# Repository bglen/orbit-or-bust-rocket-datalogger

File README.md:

# Rocket Datalogger

This is an STM32-based model rocket datalogger. It logs from the following sensors:

- DAN-F10-00B ublox dual band GNSS module
- ADXL375 high G accelerometer
- BNO055 9-DOF inertial measurement unit
- MS5607-02BA high resolution altimeter sensor
- BME280 humidity, pressure and temperature sensor

The board is powered from a single 1S LiPo battery with a standard JST-PH connector. A USB-C connector is provided for downloading the flight data. a 6-pin JST-PH connector is provided to extend the device's functionality with 6 3.3V-level GPIO pins.

The GNSS module is on a seperate PCB connected with a JST-PH connector, to give the integrated antenna the appropriate orientation (facing the sky).

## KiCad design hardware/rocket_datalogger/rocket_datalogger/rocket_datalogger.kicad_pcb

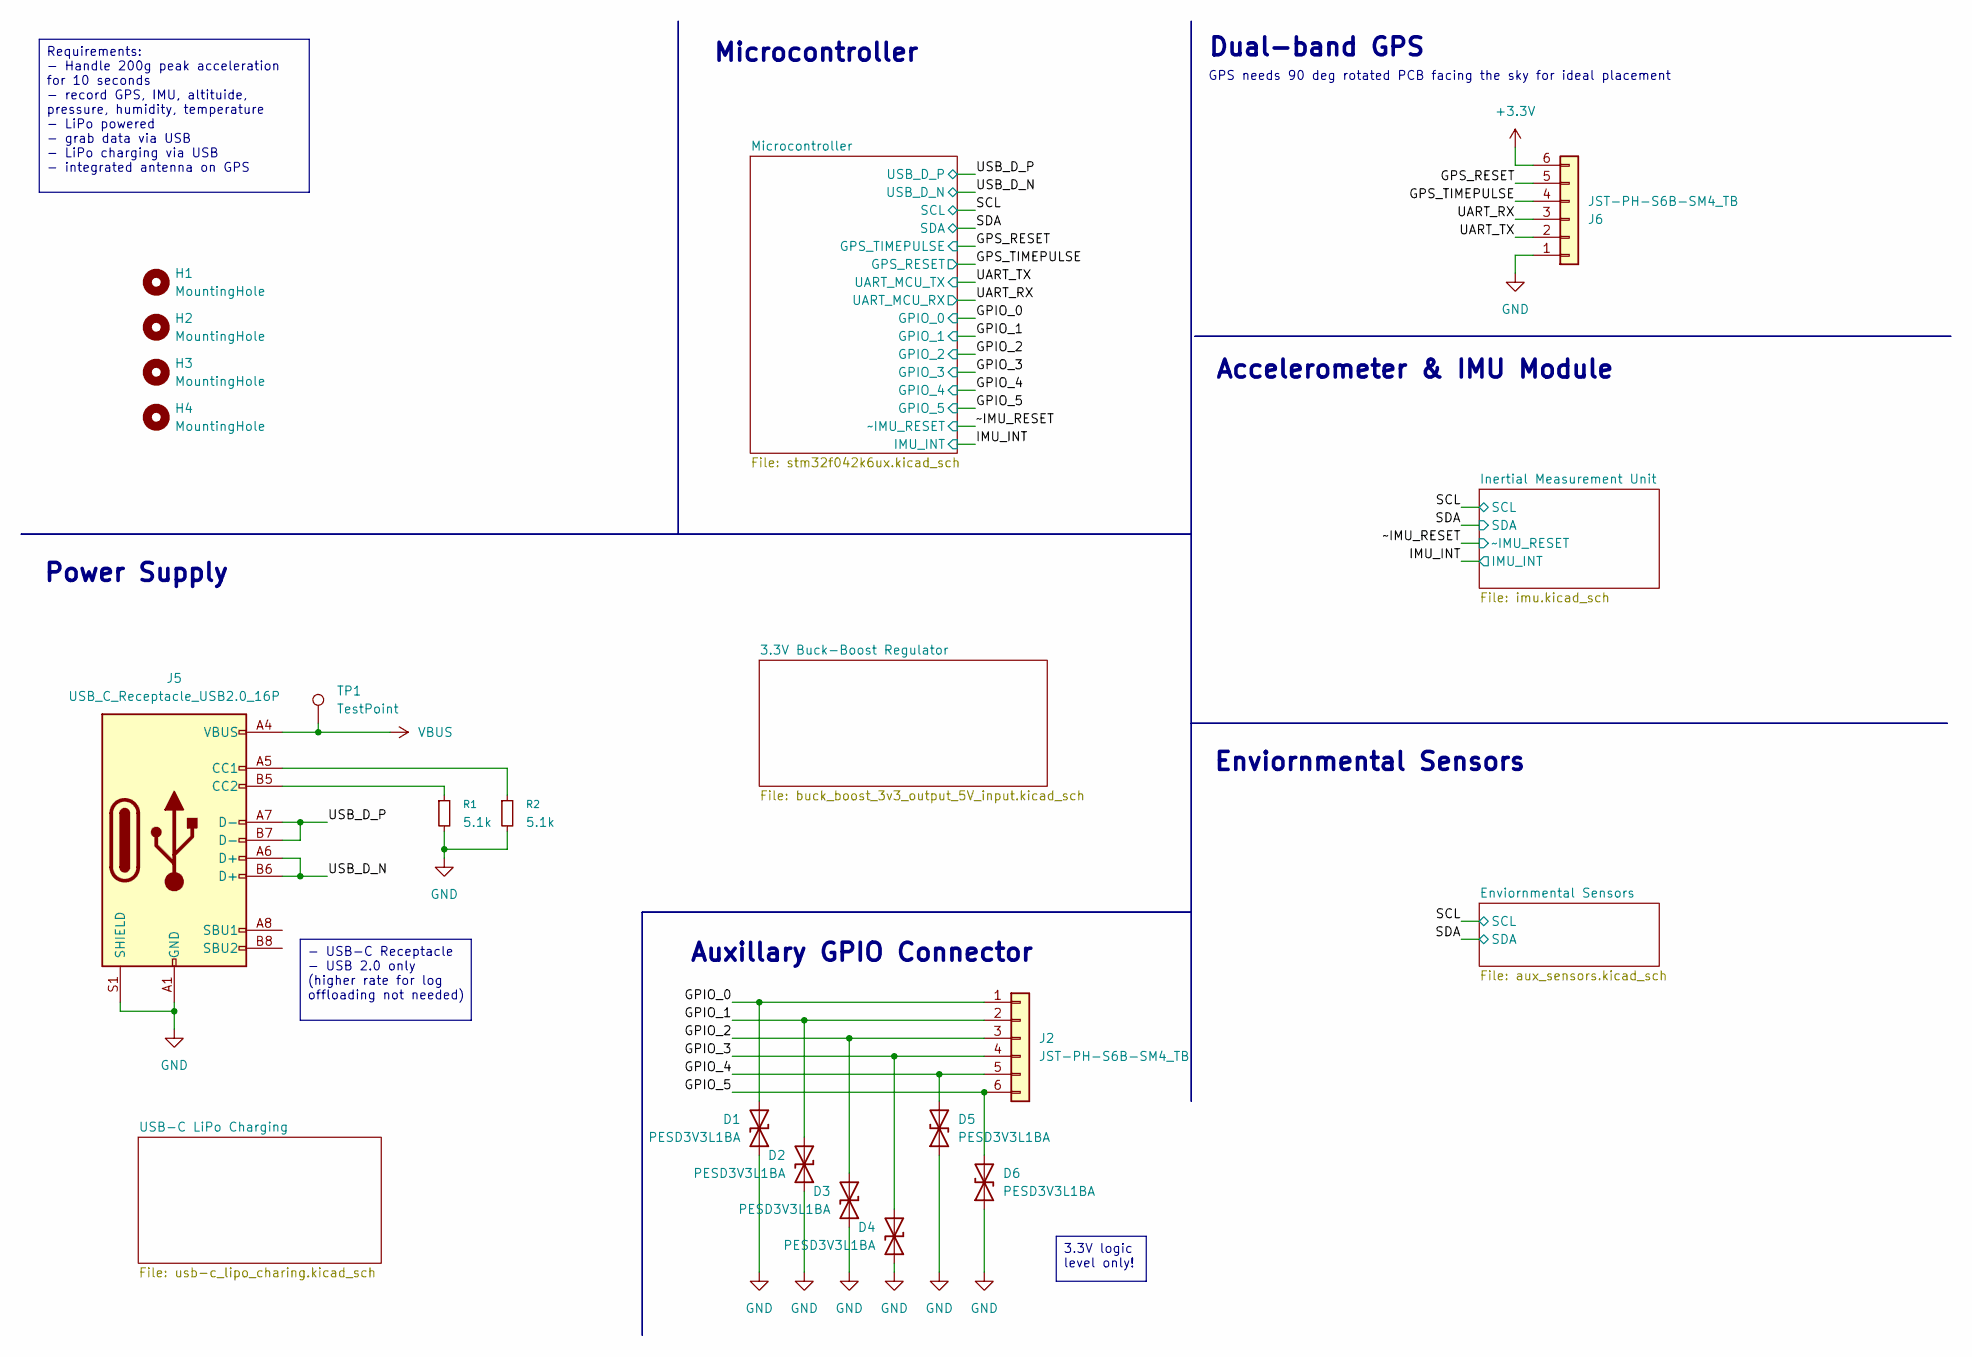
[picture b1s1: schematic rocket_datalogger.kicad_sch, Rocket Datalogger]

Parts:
D1, D2, D3, D4, D5, D6: PESD3V3L1BA; D_SOD-323
H1, H2, H3, H4: MountingHole; MountingHole_3.2mm_M3
J2, J6: JST-PH-S6B-SM4_TB; JST_PH_S6B-PH-SM4-TB_1x06-1MP_P2.00mm_Horizontal
J5: USB_C_Receptacle_USB2.0_16P; USB_C_Receptacle_GCT_USB4105-xx-A_16P_TopMnt_Horizontal
R1, R2: 5.1k; R_0603_1608Metric
TP1: TestPoint; TestPoint_Pad_D2.0mm

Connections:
+3.3V: J6.6; also elsewhere on the board
/GPIO_0: D1.2 (A2), J2.1; also elsewhere on the board
/GPIO_1: D2.2 (A2), J2.2; also elsewhere on the board
/GPIO_2: D3.2 (A2), J2.3; also elsewhere on the board
/GPIO_3: D4.2 (A2), J2.4; also elsewhere on the board
/GPIO_4: D5.2 (A2), J2.5; also elsewhere on the board
/GPIO_5: D6.2 (A2), J2.6; also elsewhere on the board
/GPS_RESET: J6.5; also elsewhere on the board
/GPS_TIMEPULSE: J6.4; also elsewhere on the board
/UART_RX: J6.3; also elsewhere on the board
/UART_TX: J6.2; also elsewhere on the board
/USB_D_N: J5.A6 (D+), J5.B6 (D+); also elsewhere on the board
/USB_D_P: J5.A7 (D-), J5.B7 (D-); also elsewhere on the board
GND: D1.1 (A1), D2.1 (A1), D3.1 (A1), D4.1 (A1), D5.1 (A1), D6.1 (A1), J5.A1 (GND), J5.A12 (GND), J5.B1 (GND), J5.B12 (GND), J5.S1 (SHIELD), J6.1, R1.2, R2.2; also elsewhere on the board
unnamed: J5.A5 (CC1), R2.1
unnamed: J5.B5 (CC2), R1.1
VBUS: J5.A4 (VBUS), J5.A9 (VBUS), J5.B4 (VBUS), J5.B9 (VBUS), TP1.1; also elsewhere on the board

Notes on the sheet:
Auxillary GPIO Connector
Dual-band GPS
Power Supply
GPS needs 90 deg rotated PCB facing the sky for ideal placement
Enviornmental Sensors
Microcontroller
Accelerometer & IMU Module
- USB-C Receptacle - USB 2.0 only (higher rate for log offloading not needed)
Requirements: - Handle 200g peak acceleration for 10 seconds - record GPS, IMU, altituide, pressure, humidity, temperature - LiPo powered - grab data via USB - LiPo charging via USB - integrated antenna on GPS
3.3V logic level only!

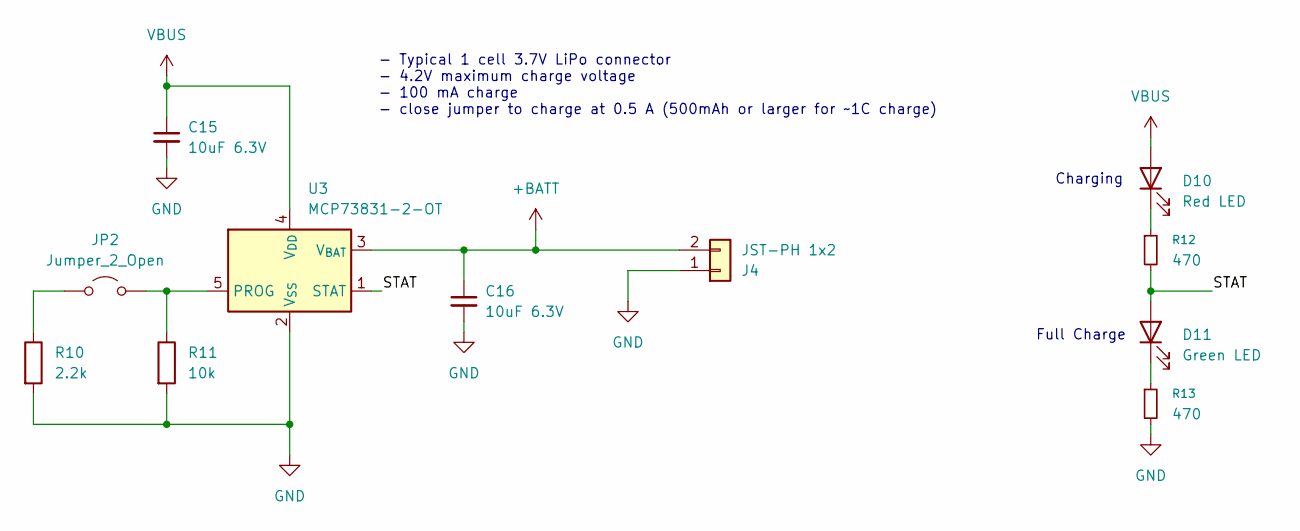
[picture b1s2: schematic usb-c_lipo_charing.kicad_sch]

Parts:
C15, C16: 10uF 6.3V; C_0603_1608Metric
D10: Red LED; LED_0603_1608Metric
D11: Green LED; LED_0603_1608Metric
J4: JST-PH 1x2; JST_PH_S2B-PH-K_1x02_P2.00mm_Horizontal
JP2: Jumper_2_Open; SolderJumper-2_P1.3mm_Open_RoundedPad1.0x1.5mm
R10: 2.2k; R_0603_1608Metric
R11: 10k; R_0603_1608Metric
R12, R13: 470; R_0603_1608Metric
U3: MCP73831-2-OT; SOT-23-5

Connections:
+BATT: C16.1, J4.2, U3.3 (V_{BAT}); also elsewhere on the board
/USB-C LiPo Charging/STAT: D11.2 (A), R12.2, U3.1 (STAT)
GND: C15.2, C16.2, J4.1, R10.2, R11.2, R13.2, U3.2 (V_{SS}); also elsewhere on the board
unnamed: D10.1 (K), R12.1
unnamed: D11.1 (K), R13.1
unnamed: JP2.1 (A), R10.1
unnamed: JP2.2 (B), R11.1, U3.5 (PROG)
VBUS: C15.1, D10.2 (A), U3.4 (V_{DD}); also elsewhere on the board

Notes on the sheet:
- Typical 1 cell 3.7V LiPo connector - 4.2V maximum charge voltage - 100 mA charge - close jumper to charge at 0.5 A (500mAh or larger for ~1C charge)
Charging
Full Charge

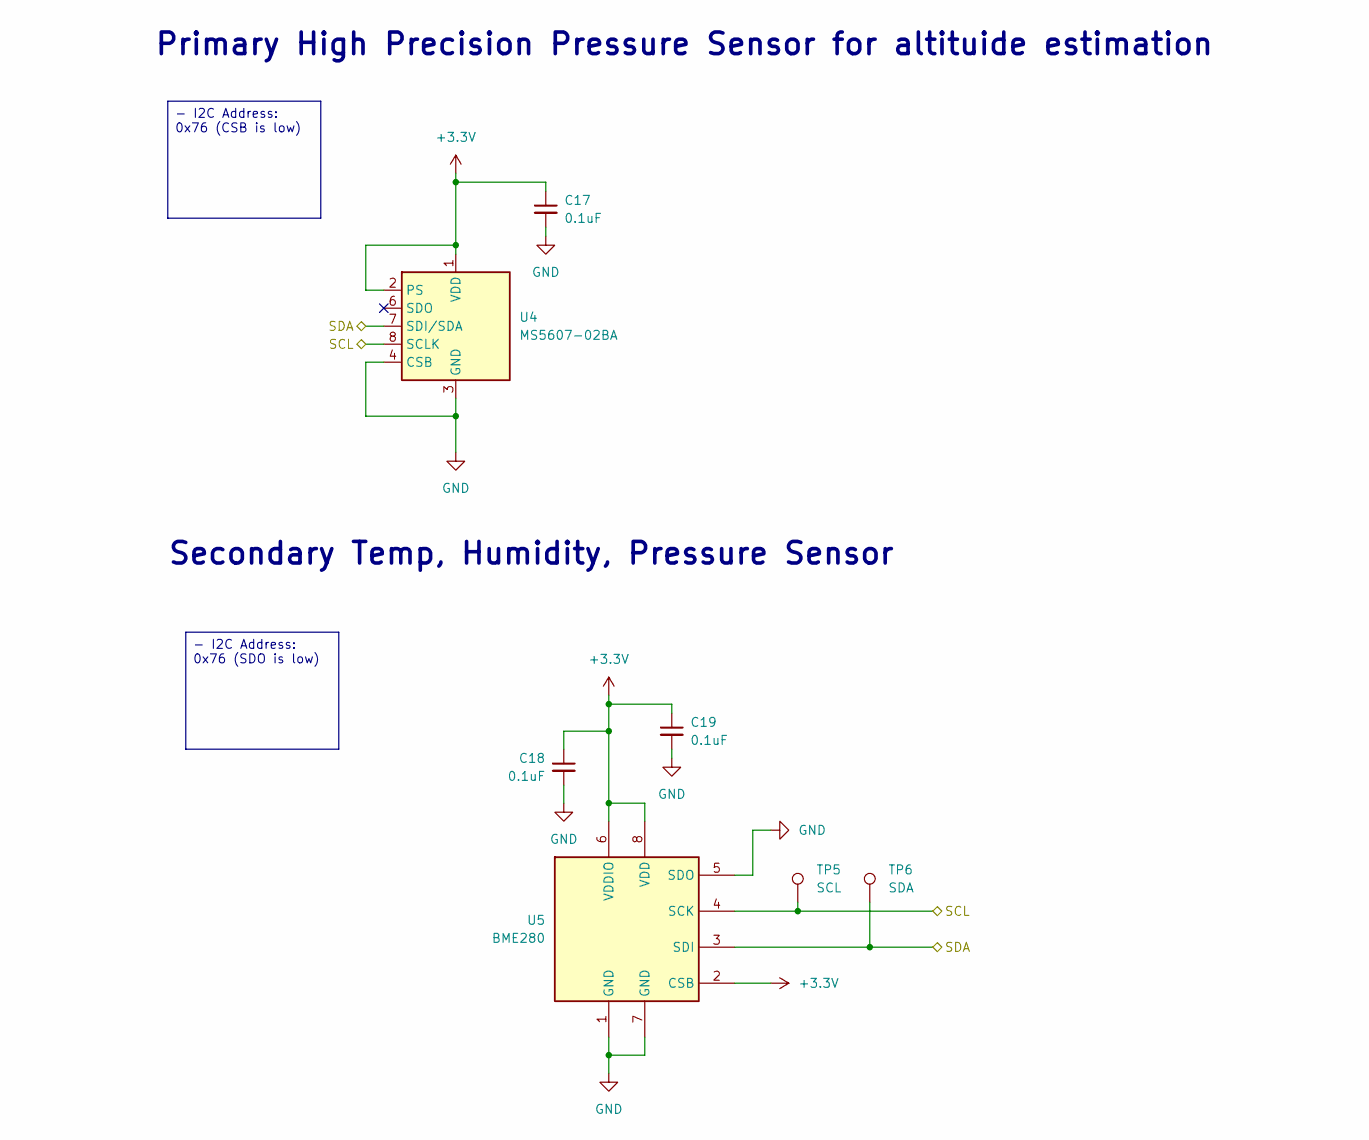
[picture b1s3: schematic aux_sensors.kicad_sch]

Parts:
C17, C18, C19: 0.1uF; C_0603_1608Metric
TP5: SCL; TestPoint_Pad_D2.0mm
TP6: SDA; TestPoint_Pad_D2.0mm
U4: MS5607-02BA; LGA-8_3x5mm_P1.25mm
U5: BME280; Bosch_LGA-8_2.5x2.5mm_P0.65mm_ClockwisePinNumbering

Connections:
+3.3V: C17.1, C18.1, C19.1, U4.1 (VDD), U4.2 (PS), U5.2 (CSB), U5.6 (VDDIO), U5.8 (VDD); also elsewhere on the board
/SCL: TP5.1, U4.8 (SCLK), U5.4 (SCK); also elsewhere on the board
/SDA: TP6.1, U4.7 (SDI/SDA), U5.3 (SDI); also elsewhere on the board
GND: C17.2, C18.2, C19.2, U4.3 (GND), U4.4 (CSB), U4.5 (CSB), U5.1 (GND), U5.5 (SDO), U5.7 (GND); also elsewhere on the board

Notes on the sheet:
Secondary Temp, Humidity, Pressure Sensor
Primary High Precision Pressure Sensor for altituide estimation
- I2C Address: 0x76 (SDO is low)
- I2C Address: 0x76 (CSB is low)

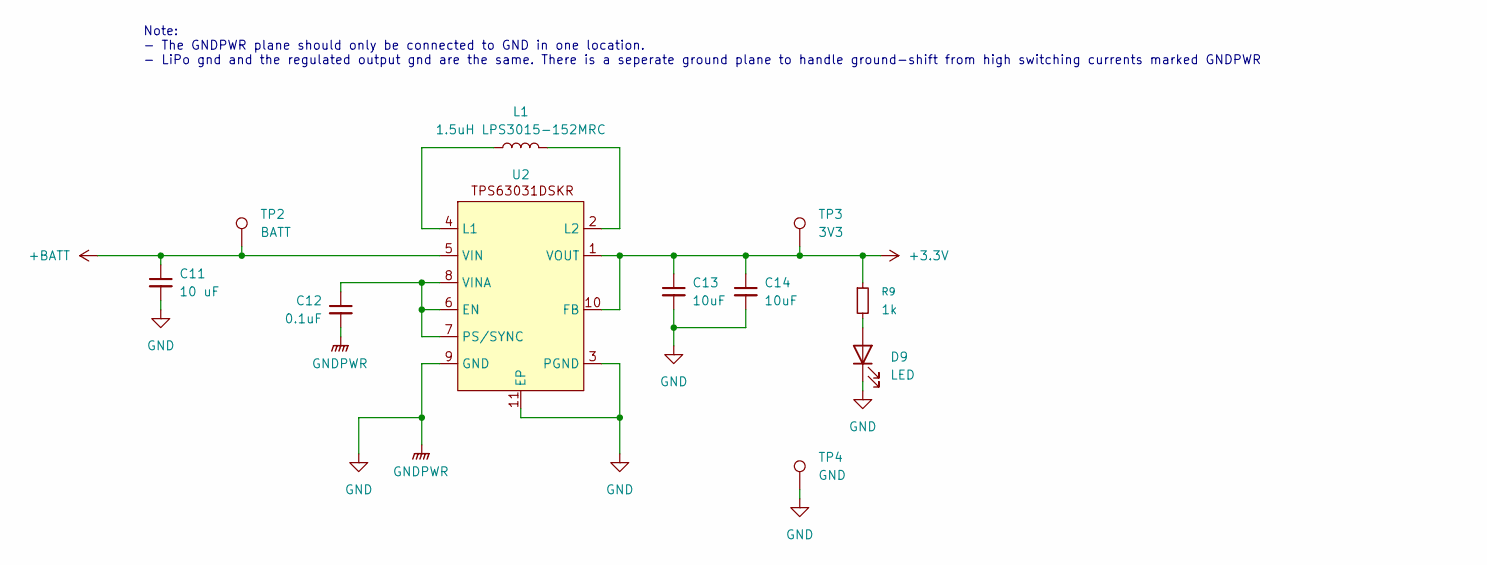
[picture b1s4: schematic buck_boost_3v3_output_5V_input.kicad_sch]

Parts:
C11: 10 uF; C_0603_1608Metric
C12: 0.1uF; C_0603_1608Metric
C13, C14: 10uF; C_0603_1608Metric
D9: LED; LED_0603_1608Metric
L1: 1.5uH LPS3015-152MRC; L_Coilcraft_LPS3010
R9: 1k; R_0603_1608Metric
TP2: BATT; TestPoint_Pad_D2.0mm
TP3: 3V3; TestPoint_Pad_D2.0mm
TP4: GND; TestPoint_Pad_D2.0mm
U2: DSK0010A

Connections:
+3.3V: C13.1, C14.1, R9.1, TP3.1, U2.1 (VOUT), U2.10 (FB); also elsewhere on the board
+BATT: C11.1, TP2.1, U2.5 (VIN); also elsewhere on the board
GND: C11.2, C12.2, C13.2, C14.2, D9.1 (K), TP4.1, U2.3 (PGND), U2.9 (GND), U2.11 (EP); also elsewhere on the board
unnamed: D9.2 (A), R9.2
unnamed: C12.1, U2.6 (EN), U2.7 (PS/SYNC), U2.8 (VINA)
unnamed: L1.1, U2.4 (L1)
unnamed: L1.2, U2.2 (L2)

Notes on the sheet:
Note: - The GNDPWR plane should only be connected to GND in one location. - LiPo gnd and the regulated output gnd are the same. There is a seperate ground plane to handle ground-shift from high switching currents marked GNDPWR

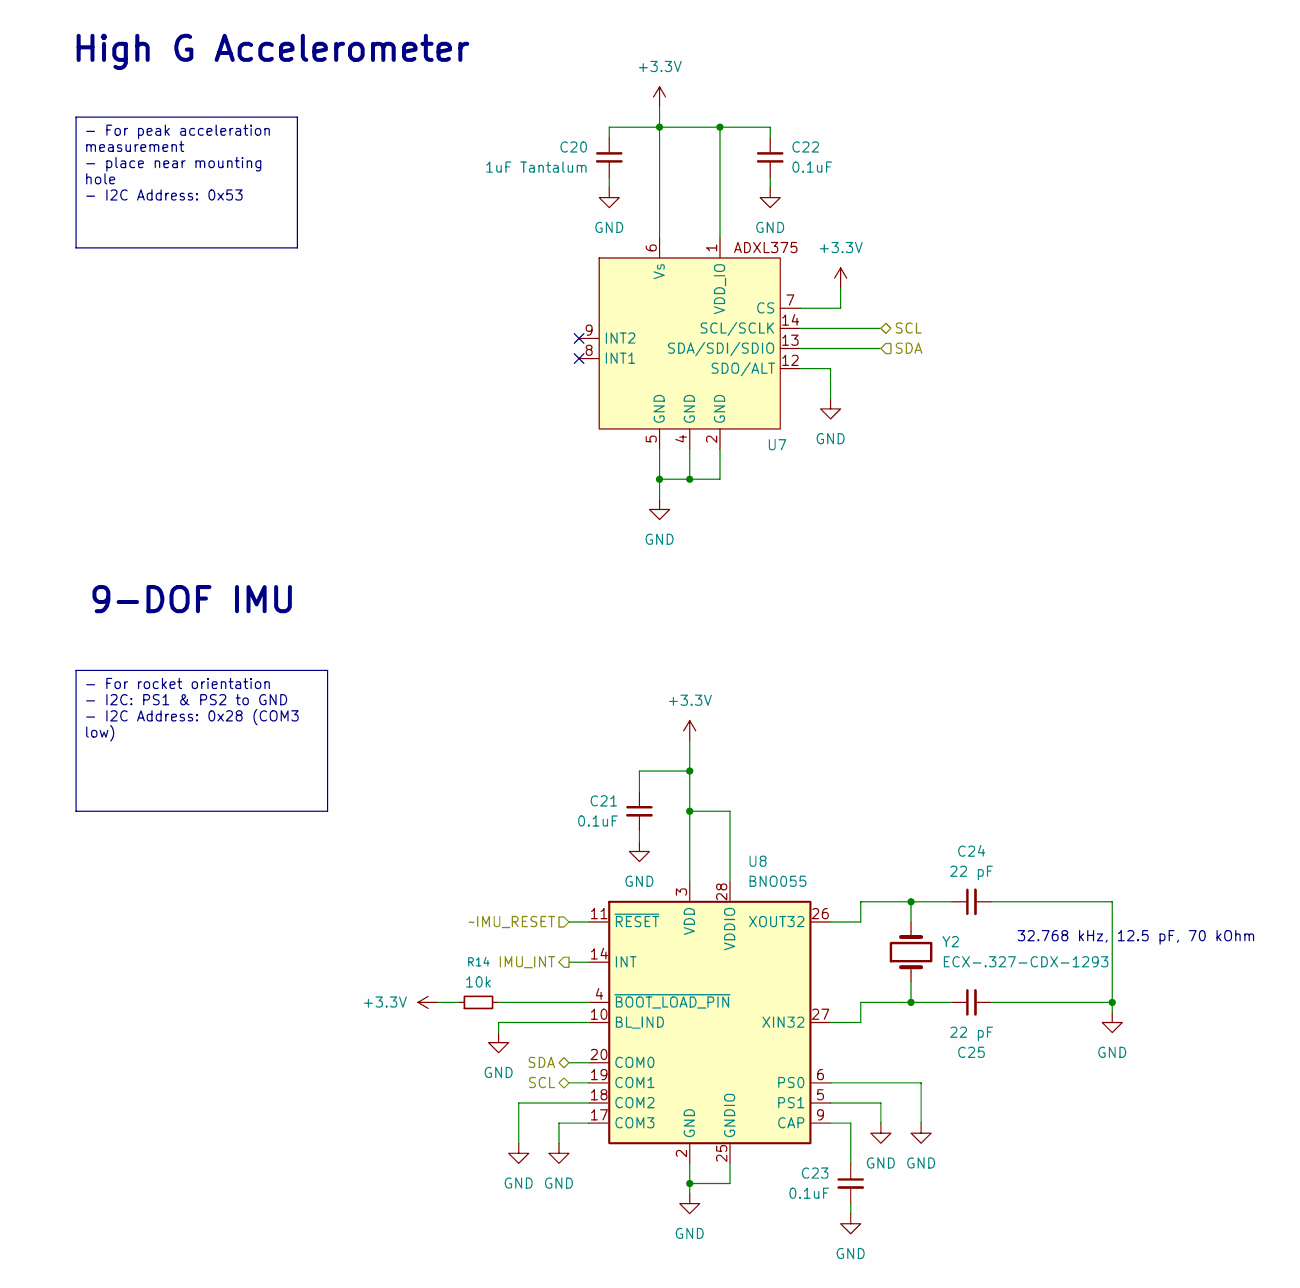
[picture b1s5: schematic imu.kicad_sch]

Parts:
C20: 1uF Tantalum; C_0603_1608Metric
C21, C22, C23: 0.1uF; C_0603_1608Metric
C24, C25: 22 pF; C_0603_1608Metric
R14: 10k; R_0603_1608Metric
U7: LGA-14_3x5mm_P0.8mm_LayoutBorder1x6y
U8: BNO055; LGA-28_5.2x3.8mm_P0.5mm
Y2: ECX-.327-CDX-1293; Crystal_SMD_3215-2Pin_3.2x1.5mm

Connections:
+3.3V: C20.1, C21.1, C22.1, R14.1, U7.1 (VDD_IO), U7.6 (Vs), U7.7 (CS), U8.3 (VDD), U8.28 (VDDIO); also elsewhere on the board
/IMU_INT: U8.14 (INT); also elsewhere on the board
/SCL: U7.14 (SCL/SCLK), U8.19 (COM1); also elsewhere on the board
/SDA: U7.13 (SDA/SDI/SDIO), U8.20 (COM0); also elsewhere on the board
/~IMU_RESET: U8.11 (~RESET); also elsewhere on the board
GND: C20.2, C21.2, C22.2, C23.2, C24.2, C25.2, U7.2 (GND), U7.4 (GND), U7.5 (GND), U7.12 (SDO/ALT), U8.2 (GND), U8.5 (PS1), U8.6 (PS0), U8.10 (BL_IND), U8.17 (COM3), U8.18 (COM2), U8.25 (GNDIO); also elsewhere on the board
unnamed: C23.1, U8.9 (CAP)
unnamed: C25.1, U8.27 (XIN32), Y2.1
unnamed: C24.1, U8.26 (XOUT32), Y2.2
unnamed: R14.2, U8.4 (~BOOT_LOAD_PIN)

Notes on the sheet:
High G Accelerometer
9-DOF IMU
32.768 kHz, 12.5 pF, 70 kOhm
- For rocket orientation - I2C: PS1 & PS2 to GND - I2C Address: 0x28 (COM3 low)
- For peak acceleration measurement - place near mounting hole - I2C Address: 0x53

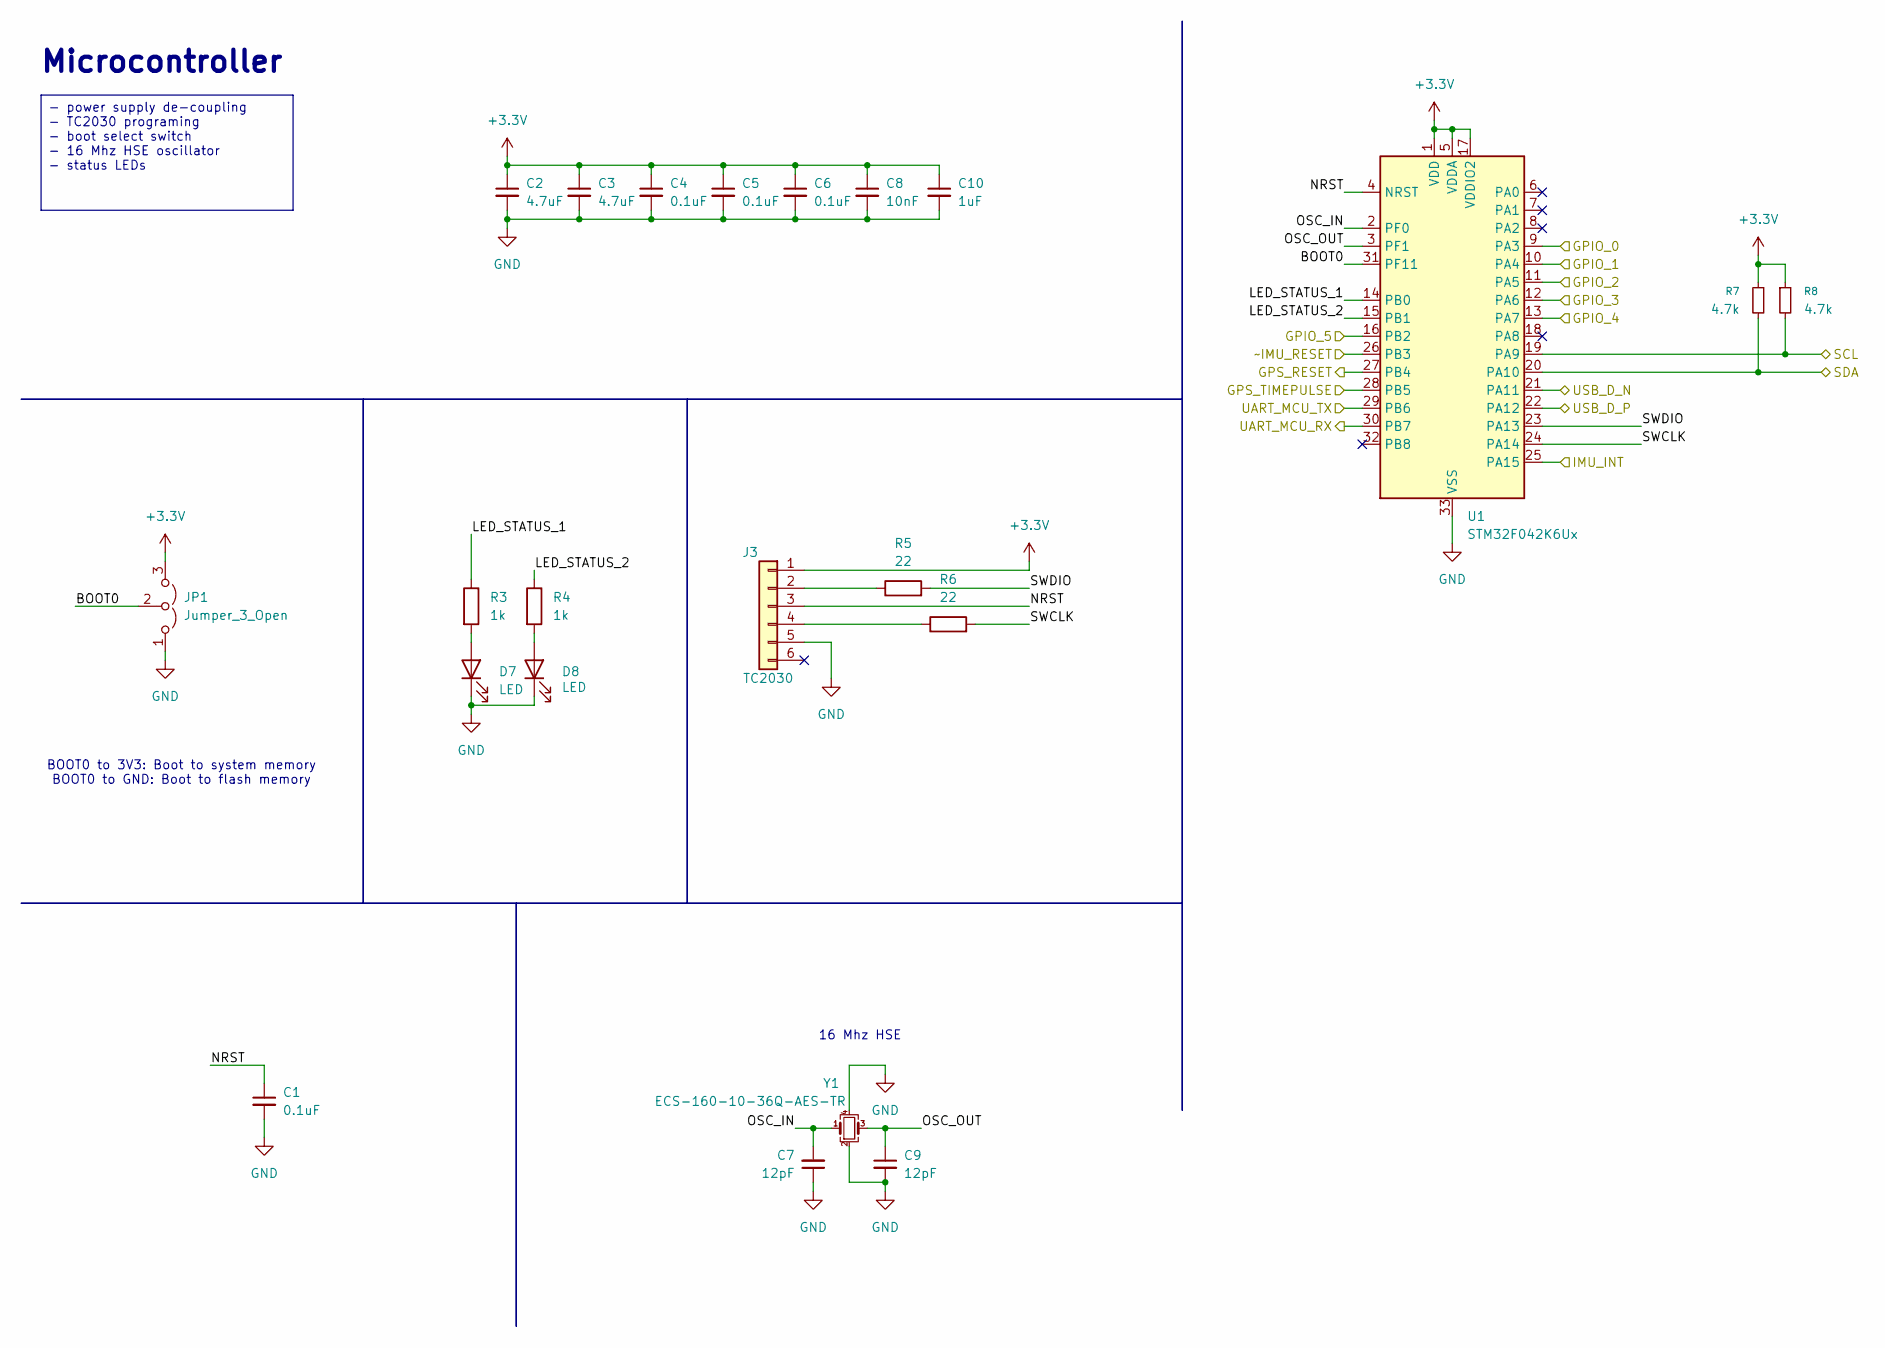
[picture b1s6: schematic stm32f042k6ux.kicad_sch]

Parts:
C1, C4, C5, C6: 0.1uF; C_0603_1608Metric
C2, C3: 4.7uF; C_0603_1608Metric
C7, C9: 12pF; C_0603_1608Metric
C8: 10nF; C_0603_1608Metric
C10: 1uF; C_0603_1608Metric
D7, D8: LED; LED_0603_1608Metric
J3: TC2030; Tag-Connect_TC2030-IDC-NL_2x03_P1.27mm_Vertical
JP1: Jumper_3_Open; SolderJumper-3_P1.3mm_Open_RoundedPad1.0x1.5mm
R3, R4: 1k; R_0603_1608Metric
R5, R6: 22; R_0603_1608Metric
R7, R8: 4.7k; R_0603_1608Metric
U1: STM32F042K6Ux; QFN-32-1EP_5x5mm_P0.5mm_EP3.45x3.45mm
Y1: ECS-160-10-36Q-AES-TR; Crystal_SMD_2520-4Pin_2.5x2.0mm

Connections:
+3.3V: C2.1, C3.1, C4.1, C5.1, C6.1, C8.1, C10.1, J3.1, JP1.3 (B), R7.1, R8.1, U1.1 (VDD), U1.5 (VDDA), U1.17 (VDDIO2); also elsewhere on the board
/GPIO_0: U1.9 (PA3); also elsewhere on the board
/GPIO_1: U1.10 (PA4); also elsewhere on the board
/GPIO_2: U1.11 (PA5); also elsewhere on the board
/GPIO_3: U1.12 (PA6); also elsewhere on the board
/GPIO_4: U1.13 (PA7); also elsewhere on the board
/GPIO_5: U1.16 (PB2); also elsewhere on the board
/GPS_RESET: U1.28 (PB5); also elsewhere on the board
/GPS_TIMEPULSE: U1.27 (PB4); also elsewhere on the board
/IMU_INT: U1.25 (PA15); also elsewhere on the board
/Microcontroller/BOOT0: JP1.2 (C), U1.31 (PF11)
/Microcontroller/LED_STATUS_1: R3.1, U1.14 (PB0)
/Microcontroller/LED_STATUS_2: R4.1, U1.15 (PB1)
/Microcontroller/NRST: C1.1, J3.3, U1.4 (NRST)
/Microcontroller/OSC_IN: C7.2, U1.2 (PF0), Y1.1
/Microcontroller/OSC_OUT: C9.1, U1.3 (PF1), Y1.3
/Microcontroller/SWCLK: R6.2, U1.24 (PA14)
/Microcontroller/SWDIO: R5.2, U1.23 (PA13)
/SCL: R8.2, U1.19 (PA9); also elsewhere on the board
/SDA: R7.2, U1.20 (PA10); also elsewhere on the board
/UART_RX: U1.30 (PB7); also elsewhere on the board
/UART_TX: U1.29 (PB6); also elsewhere on the board
/USB_D_N: U1.21 (PA11); also elsewhere on the board
/USB_D_P: U1.22 (PA12); also elsewhere on the board
/~IMU_RESET: U1.26 (PB3); also elsewhere on the board
GND: C1.2, C2.2, C3.2, C4.2, C5.2, C6.2, C7.1, C8.2, C9.2, C10.2, D7.1 (K), D8.1 (K), J3.5, JP1.1 (A), U1.33 (VSS), Y1.2, Y1.4; also elsewhere on the board
unnamed: D7.2 (A), R3.2
unnamed: D8.2 (A), R4.2
unnamed: J3.2, R5.1
unnamed: J3.4, R6.1

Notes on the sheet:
BOOT0 to 3V3: Boot to system memory BOOT0 to GND: Boot to flash memory
Microcontroller
16 Mhz HSE
- power supply de-coupling - TC2030 programing - boot select switch - 16 Mhz HSE oscillator - status LEDs

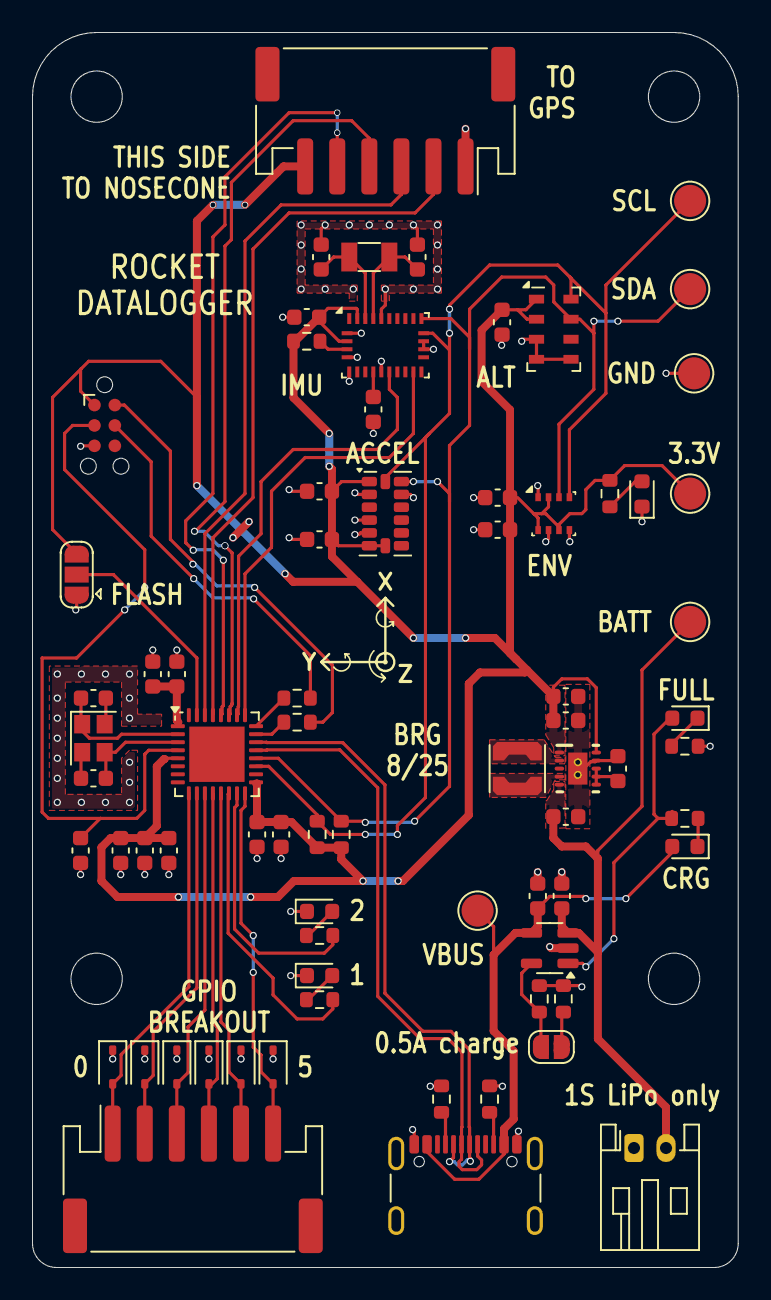
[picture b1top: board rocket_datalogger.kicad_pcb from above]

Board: 2 copper layers, 44.0 x 77.0 mm, 77 parts (0 on the bottom side), 47 nets.

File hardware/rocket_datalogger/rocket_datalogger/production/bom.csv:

Designator,Footprint,Quantity,Value,LCSC Part #
"C1, C12, C17, C18, C19, C21, C22, C23, C4, C5, C6",0603,11,0.1uF,
C10,0603,1,1uF,
C11,0603,1,10 uF,
"C13, C14",0603,2,10uF,
"C15, C16",0603,2,10uF 6.3V,
"C2, C3",0603,2,4.7uF,
C20,0603,1,1uF Tantalum,
"C24, C25",0603,2,22 pF,
"C7, C9",0603,2,12pF,
C8,0603,1,10nF,
"D1, D2, D3, D4, D5, D6",D_SOD-323,6,PESD3V3L1BA,
D10,0603,1,Red LED,
D11,0603,1,Green LED,
"D7, D8, D9",0603,3,LED,
"J2, J6",JST_PH_S6B-PH-SM4-TB_1x06-1MP_P2.00mm_Horizontal,2,JST-PH-S6B-SM4_TB,
J3,Tag-Connect_TC2030-IDC-NL_2x03_P1.27mm_Vertical,1,TC2030,
J4,JST_PH_S2B-PH-K_1x02_P2.00mm_Horizontal,1,JST-PH 1x2,
J5,USB_C_Receptacle_GCT_USB4105-xx-A_16P_TopMnt_Horizontal,1,USB_C_Receptacle_USB2.0_16P,
JP1,SolderJumper-3_P1.3mm_Open_RoundedPad1.0x1.5mm,1,Jumper_3_Open,
JP2,SolderJumper-2_P1.3mm_Open_RoundedPad1.0x1.5mm,1,Jumper_2_Open,
L1,L_Coilcraft_LPS3010,1,1.5uH LPS3015-152MRC,
"R1, R2",0603,2,5.1k,
R10,0603,1,2.2k,
"R11, R14",0603,2,10k,
"R12, R13",0603,2,470,
"R3, R4, R9",0603,3,1k,
"R5, R6",0603,2,22,
"R7, R8",0603,2,4.7k,
TP1,TestPoint_Pad_D2.0mm,1,TestPoint,
TP2,TestPoint_Pad_D2.0mm,1,BATT,
TP3,TestPoint_Pad_D2.0mm,1,3V3,
TP4,TestPoint_Pad_D2.0mm,1,GND,
TP5,TestPoint_Pad_D2.0mm,1,SCL,
TP6,TestPoint_Pad_D2.0mm,1,SDA,
U1,QFN-32-1EP_5x5mm_P0.5mm_EP3.45x3.45mm,1,STM32F042K6Ux,
U2,DSK0010A,1,~,
U3,SOT-23-5,1,MCP73831-2-OT,
U4,LGA-8_3x5mm_P1.25mm,1,MS5607-02BA,
U5,Bosch_LGA-8_2.5x2.5mm_P0.65mm_ClockwisePinNumbering,1,BME280,
U7,LGA-14_3x5mm_P0.8mm_LayoutBorder1x6y,1,~,
U8,LGA-28_5.2x3.8mm_P0.5mm,1,BNO055,
Y1,Crystal_SMD_2520-4Pin_2.5x2.0mm,1,ECS-160-10-36Q-AES-TR,
Y2,Crystal_SMD_3215-2Pin_3.2x1.5mm,1,ECX-.327-CDX-1293,

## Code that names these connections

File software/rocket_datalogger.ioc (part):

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Mcu.Name=STM32F042K(4-6)Ux
Mcu.Package=UFQFPN32
Mcu.UserName=STM32F042K6Ux
PA0.GPIOParameters=GPIO_Label
PA0.GPIO_Label=GPS_RESET
PA0.Signal=GPIO_Output
PA1.GPIOParameters=GPIO_Label
PA1.GPIO_Label=GPS_TIMEPULSE
PA1.Signal=GPIO_Input
PA10.Mode=I2C
PA10.Signal=I2C1_SDA
PA11.Mode=Device
PA11.Signal=USB_DM
PA12.Mode=Device
PA12.Signal=USB_DP
PA2.GPIOParameters=GPIO_Label
PA2.GPIO_Label=IMU_ADDRESS_SELECT
PA2.Signal=GPIO_Output
PA3.GPIOParameters=GPIO_Label
PA3.GPIO_Label=GPIO_0
PA3.Signal=GPIO_Output
PA4.GPIOParameters=GPIO_Label
PA4.GPIO_Label=GPIO_1
PA4.Signal=GPIO_Output
PA5.GPIOParameters=GPIO_Label
PA5.GPIO_Label=GPIO_2
PA5.Signal=GPIO_Output
PA6.GPIOParameters=GPIO_Label
PA6.GPIO_Label=GPIO_3
PA6.Signal=GPIO_Output
PA7.GPIOParameters=GPIO_Label
PA7.GPIO_Label=GPIO_4
PA7.Signal=GPIO_Output
PA9.Mode=I2C
PA9.Signal=I2C1_SCL
PB0.GPIOParameters=GPIO_Label
PB0.GPIO_Label=LED_STATUS_1
PB0.Signal=GPIO_Output
PB1.GPIOParameters=GPIO_Label
PB1.GPIO_Label=LED_STATUS_2
PB1.Signal=GPIO_Output
PB2.GPIOParameters=GPIO_Label
PB2.GPIO_Label=GPIO_5
PB2.Signal=GPIO_Output
PB6.Mode=Asynchronous
PB6.Signal=USART1_TX
PB7.Mode=Asynchronous
PB7.Signal=USART1_RX
PF0-OSC_IN.Mode=HSE-External-Oscillator
PF0-OSC_IN.Signal=RCC_OSC_IN
PF1-OSC_OUT.Mode=HSE-External-Oscillator
PF1-OSC_OUT.Signal=RCC_OSC_OUT
RCC.HSE_VALUE=16000000
RCC.SYSCLKFreq_VALUE=48000000
RCC.SYSCLKSource=RCC_SYSCLKSOURCE_PLLCLK
board=custom

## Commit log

2025-08-18 Initial hardware commit
2025-08-19 software initial commit
2025-08-19 Changed IMU to BNO055
    Previous IMU required 1.85V rail
2025-08-19 fixed minor hardware issues
2025-08-19 Minor revision
2025-08-19 PCB design rev 1
2025-08-19 GNSS Antenna board
2025-08-19 Updated BOM and schematic notes
2025-08-20 PCB step files
